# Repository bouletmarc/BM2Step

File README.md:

# BM2Step
Arduino based 2Step Launch Control Module similar to Bee*R for Honda/Acura

# Compatibility

- All Honda/Acura engines that are 4cylinder and running with a distributor (mainly SerieB, D, F and H engines).
- It does works on Automatics cars.

# Parts List
- 1x Arduino Nano V3 5V 16mhz atmega328p
- 1x 74HC00 Quad 2-input NAND gate (or 74LVC1G00 for a Single gate rather than a Quad gate)
- 2x 2N4401 transistors (2N2222/2N3904 can be used)
- 6x 1K Ohms resistors
- 1x 1 to 10 Ohm resistors (can be replaced with a jumper or '0ohm' directly but a resistor make the circuit safer!)
- 2x B10K Potentiometer 0931
- 2x 2mm to 5mm Leds
- 1x 7805/78M05 5v voltage regulator
- 2x 100nF capacitor (104)
- 1x Diode (minimum of 20v), can be 1N4002, 1N4004, 1N4148, etc..

# Installation

Inputs wires:
- ICM - Ignition Control Module signal from the ECU
- Potentiometer - Launch RPM selection
- Potentiometer - Cut RPM selection
- Activate Launch/2Step (sort to ground to activate)
- 12v Ignition On
- Ground

Outputs wires:
- ICM - Ignition Control Module singal Out for the distributor

**You don't need to power the arduino from the USB, the 7805/78M05 5v regulator output 5v from the 12v Ignition input wire to power the arduino when the Car ignition key are turned On!**

# How to use the BM2Step

1. Choose your desired Launch Control 2Step RPM with the potentiometer
2. Choose your desired Launch Control 2Step Cutting rpm windows with the potentiometer
3. Activate the Launch/2Step by sorting the Activate 'input' to the ground
4. Bring the engine RPM to the desired Launch Control 2Step RPM
5. Enjoy!

# How the BM2Step works

The BM2Step works by disabling the ICM ouputs when the BM2Step are active and the engine rpm reach the Set RPM. The diagram have 2x 2n4401 transistors to control the direction of the ICM outputs. One transistor are sending the ICM signal back to the distributor (sending to the ICM ouputs on the BM2Step) while the other transistor are sending the ICM signal in a 'built-in distributor simulator'.

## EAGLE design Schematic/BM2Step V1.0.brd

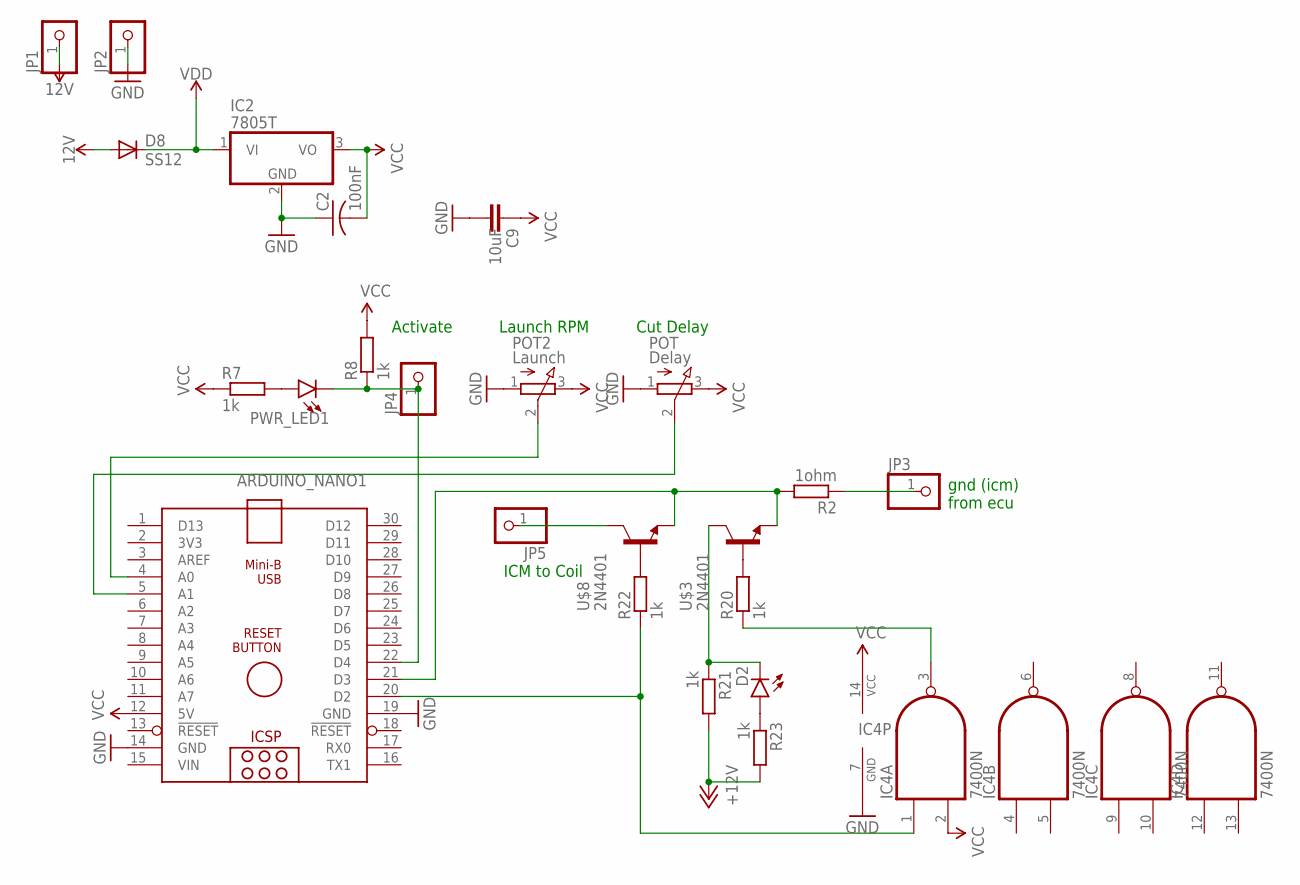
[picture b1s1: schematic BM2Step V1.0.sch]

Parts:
ARDUINO_NANO1: ARDUINO_NANO
C2: 100nF; C025-024X044
C9: 10uF; AXIAL-5MM
D2: LED3MM
D8: SS12; D-7.5
IC2: 7805T; TO220H
IC4: 7400N; DIL14
JP1, JP2, JP3, JP4, JP5: PINHD-1X1_LARGE; 1X01_LARGE
POT: Delay; EVUF
POT2: Launch; EVUF
PWR_LED1: LED3MM; LED_3MM
R2: 1ohm; 0204/7
R7, R8, R20, R21, R22, R23: 1k; 0204/7
U$3, U$8: 2N4401; TO92-ECB

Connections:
12V: D8.A, JP1.1
+12V: R21.2, R23.2
GND: ARDUINO_NANO1.14 (GND), ARDUINO_NANO1.19 (GND), C2.1, C9.P$2 (2), IC2.2 (GND), IC4.7 (GND), JP2.1, POT.1 (A), POT2.1 (A)
unnamed: IC4.3 (O), R20.1
unnamed: ARDUINO_NANO1.22 (D4), JP4.1, PWR_LED1.K (C), R8.1
unnamed: ARDUINO_NANO1.4 (A0), POT2.2 (S)
unnamed: ARDUINO_NANO1.5 (A1), POT.2 (S)
unnamed: JP3.1, R2.1
unnamed: ARDUINO_NANO1.21 (D3), R2.2, U$3.E, U$8.E
unnamed: PWR_LED1.A, R7.2
unnamed: R20.2, U$3.B
unnamed: D2.K (C), R21.1, U$3.C
unnamed: JP5.1, U$8.C
unnamed: R22.2, U$8.B
unnamed: ARDUINO_NANO1.20 (D2), IC4.1 (I0), R22.1
unnamed: D2.A, R23.1
VCC: ARDUINO_NANO1.12 (5V), C2.2, C9.P$1 (1), IC2.3 (VO), IC4.2 (I1), IC4.14 (VCC), POT.3 (E), POT2.3 (E), R7.1, R8.2
VDD: D8.C, IC2.1 (VI)
VIN: ARDUINO_NANO1.15 (VIN)

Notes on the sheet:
gnd (icm) from ecu
ICM to Coil
Launch RPM
Cut Delay
Activate

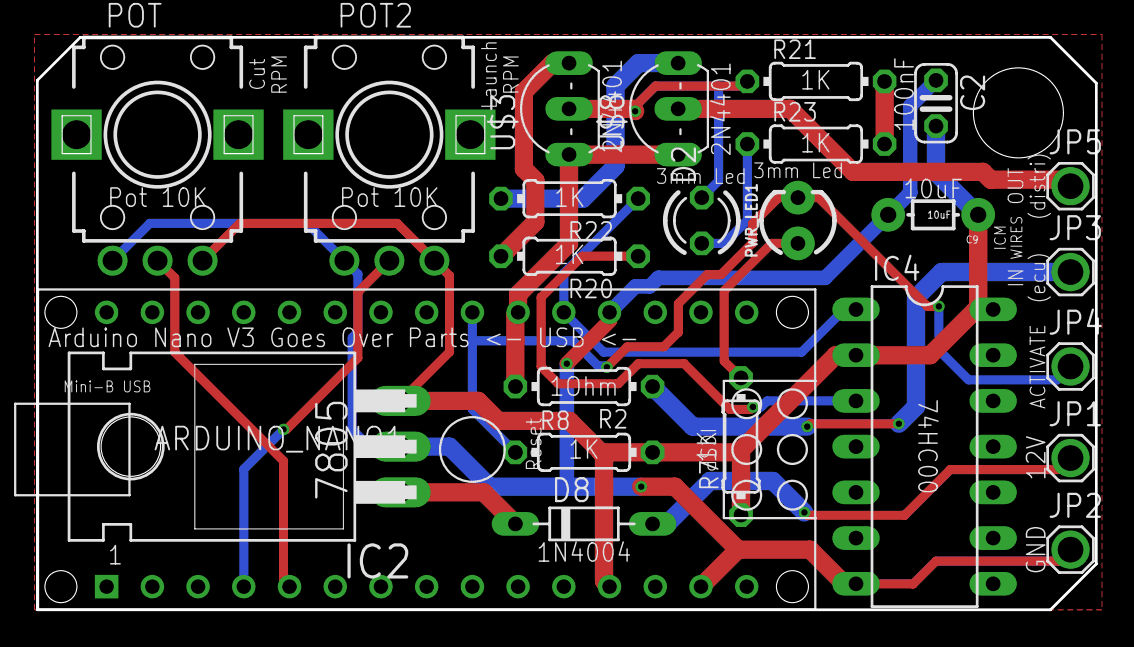
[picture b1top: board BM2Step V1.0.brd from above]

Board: 2 copper layers, 58.8 x 31.8 mm, 24 parts (0 on the bottom side), 18 nets.

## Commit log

2020-05-11 V1.0 first upload
2020-05-11 V1.0 Added missing Activate Input

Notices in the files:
parts and their libraries:
SparkFun-LED: Licensing: Creative Commons ShareAlike 4.0 International - https://creativecommons.org/licenses/by-sa/4.0
SparkFun: Licensing: CC v3.0 Share-Alike You are welcome to use this library for commercial purposes.
